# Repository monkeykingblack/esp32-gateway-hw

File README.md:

#ESP32-GATEWAY-HARDWARE

##Features

- ESP32 WIFI, Bluetooth LE, SoC - 240MHz - Module ESP32 Wrover
- Tracking location by GPS-NEO-6M IC
- Send SMS via sim card by 
- Automatic select 3 power sources (DC6-28V, USB and Battery)
- Charger battery lithium 3.7V
- 1 Power LED, 1 Status GPS LED, 1 Status GSM LED

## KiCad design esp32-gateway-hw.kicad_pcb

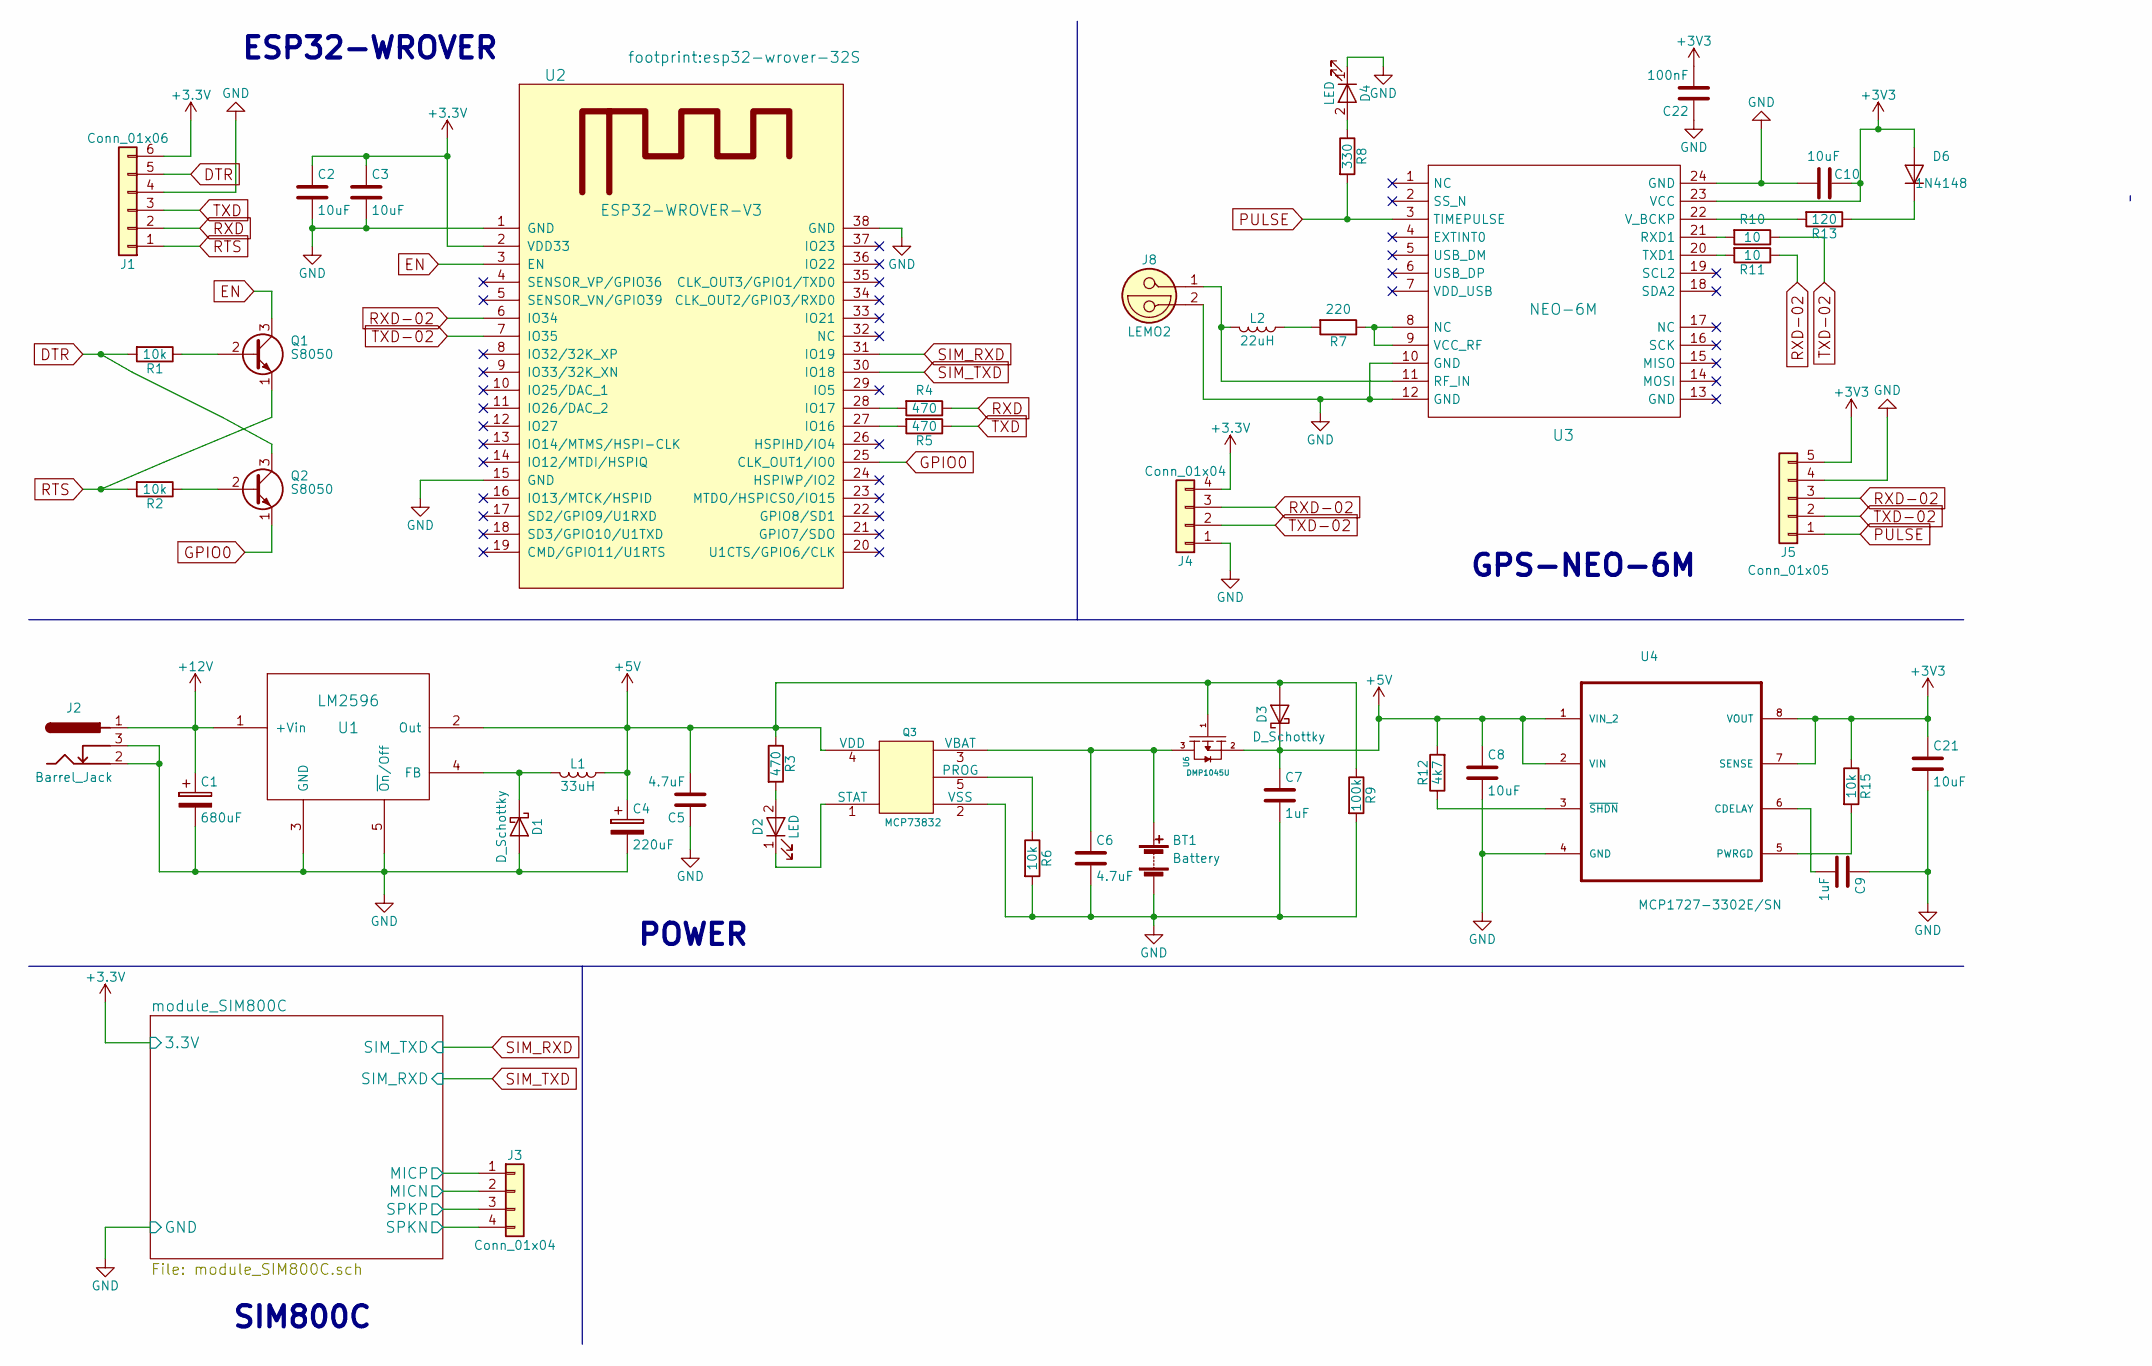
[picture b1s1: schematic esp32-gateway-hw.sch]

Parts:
BT1: Battery; JST_EH_B02B-EH-A_02x2.50mm_Straight
C1: 680uF; CP_Elec_4x5.3
C2, C3, C8, C10, C21: 10uF; C_0603
C4: 220uF; CP_Elec_4x5.3
C5, C6: 4.7uF; C_0603
C7, C9: 1uF; C_0603
C22: 100nF; C_0603
D1, D3: D_Schottky; D_SOD-123
D2, D4: LED; LED_D3.0mm
D6: 1N4148; D_SOD-123
J1: Conn_01x06; Socket_Strip_Straight_1x06_Pitch2.54mm
J2: Barrel_Jack; CUI-PJ-102A_dc-barrel-jack
J3, J4: Conn_01x04; Socket_Strip_Straight_1x04_Pitch2.54mm
J5: Conn_01x05; Socket_Strip_Straight_1x05_Pitch2.54mm
J8: LEMO2; SMA_Straight
L1: 33uH; INDUCTOR_SMD_DIP2
L2: 22uH; INDUCTOR_SMD_DIP2
Q1, Q2: S8050; SOT-23_standar
Q3: MCP73832; SOT-23-5_HandSoldering
R1, R2, R6, R15: 10k; R_0603
R3, R4, R5: 470; R_0603
R7: 220; R_0603
R8: 330; R_0603
R9: 100k; R_0603
R10, R11: 10; R_0603
R12: 4k7; R_0603
R13: 120; R_0603
U1: LM2596; TO-263-5_TabPin3
U2: ESP32-WROVER-V3; esp32-wrover-32S
U3: NEO-6M; GPS24P-SMD-1.1-16X12.2MM
U4: MCP1727-3302E/SN; SOIC-8_3.9x4.9mm_Pitch1.27mm; Digi-Key_Part_Number MCP1727-3302E/SN-ND
U6: DMP1045U; SOT-23

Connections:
+3V3: C2.1, C3.1, C10.1, C21.1, C22.2, D6.2 (A), J1.6, J4.4, J5.5, R15.1, U2.2 (VDD33), U3.23 (VCC), U4.7 (SENSE), U4.8 (VOUT); also elsewhere on the board
+5V: C4.1, C5.2, C7.1, C8.1, D3.1 (K), D3.2 (A), L1.1, Q3.4 (VDD), R3.1, R9.1, R12.2, U1.2 (Out), U4.1 (VIN_2), U4.2 (VIN), U6.1, U6.2
+12V: C1.1, J2.1, U1.1 (+Vin)
/module_SIM800C/MICN: J3.2; also elsewhere on the board
/module_SIM800C/MICP: J3.1; also elsewhere on the board
/module_SIM800C/SPKN: J3.4; also elsewhere on the board
/module_SIM800C/SPKP: J3.3; also elsewhere on the board
DTR: J1.5, Q2.3 (C), R1.2
EN: Q1.3 (C), U2.3 (EN)
GND: BT1.2 (-), C1.2, C2.2, C3.2, C4.2, C5.1, C6.2, C7.2, C8.2, C9.1, C10.2, C21.2, C22.1, D1.2 (A), D4.1 (K), J1.4, J2.2, J2.3, J4.1, J5.4, J8.2, Q3.2 (VSS), R6.2, R9.2, U1.3 (GND), U1.5 (~On~/Off), U2.1 (GND), U2.15 (GND), U2.38 (GND), U3.10 (GND), U3.12 (GND), U3.24 (GND), U4.4 (GND); also elsewhere on the board
GPIO0: Q2.1 (E), U2.25 (CLK_OUT1/IO0)
unnamed: BT1.1 (+), C6.1, Q3.3 (VBAT), U6.3
unnamed: C9.2, U4.6 (CDELAY)
unnamed: D1.1 (K), L1.2, U1.4 (FB)
unnamed: D2.1 (K), Q3.1 (STAT)
unnamed: D2.2 (A), R3.2
unnamed: D4.2 (A), R8.1
unnamed: D6.1 (K), R13.1
unnamed: J8.1, L2.2, U3.11 (RF_IN)
unnamed: L2.1, R7.2
unnamed: Q1.2 (B), R1.1
unnamed: Q2.2 (B), R2.1
unnamed: Q3.5 (PROG), R6.1
unnamed: R4.2, U2.28 (IO17)
unnamed: R5.2, U2.27 (IO16)
unnamed: R7.1, U3.8 (NC), U3.9 (VCC_RF)
unnamed: R10.2, U3.21 (RXD1)
unnamed: R11.2, U3.20 (TXD1)
unnamed: R12.1, U4.3 (~SHDN)
unnamed: R13.2, U3.22 (V_BCKP)
unnamed: R15.2, U4.5 (PWRGD)
PULSE: J5.1, R8.2, U3.3 (TIMEPULSE)
RTS: J1.1, Q1.1 (E), R2.2
RXD: J1.2, R4.1
RXD-02: J4.3, J5.3, R11.1, U2.6 (IO34)
SIM_RXD: U2.31 (IO19); also elsewhere on the board
SIM_TXD: U2.30 (IO18); also elsewhere on the board
TXD: J1.3, R5.1
TXD-02: J4.2, J5.2, R10.1, U2.7 (IO35)

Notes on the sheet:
ESP32-WROVER
GPS-NEO-6M
POWER
SIM800C

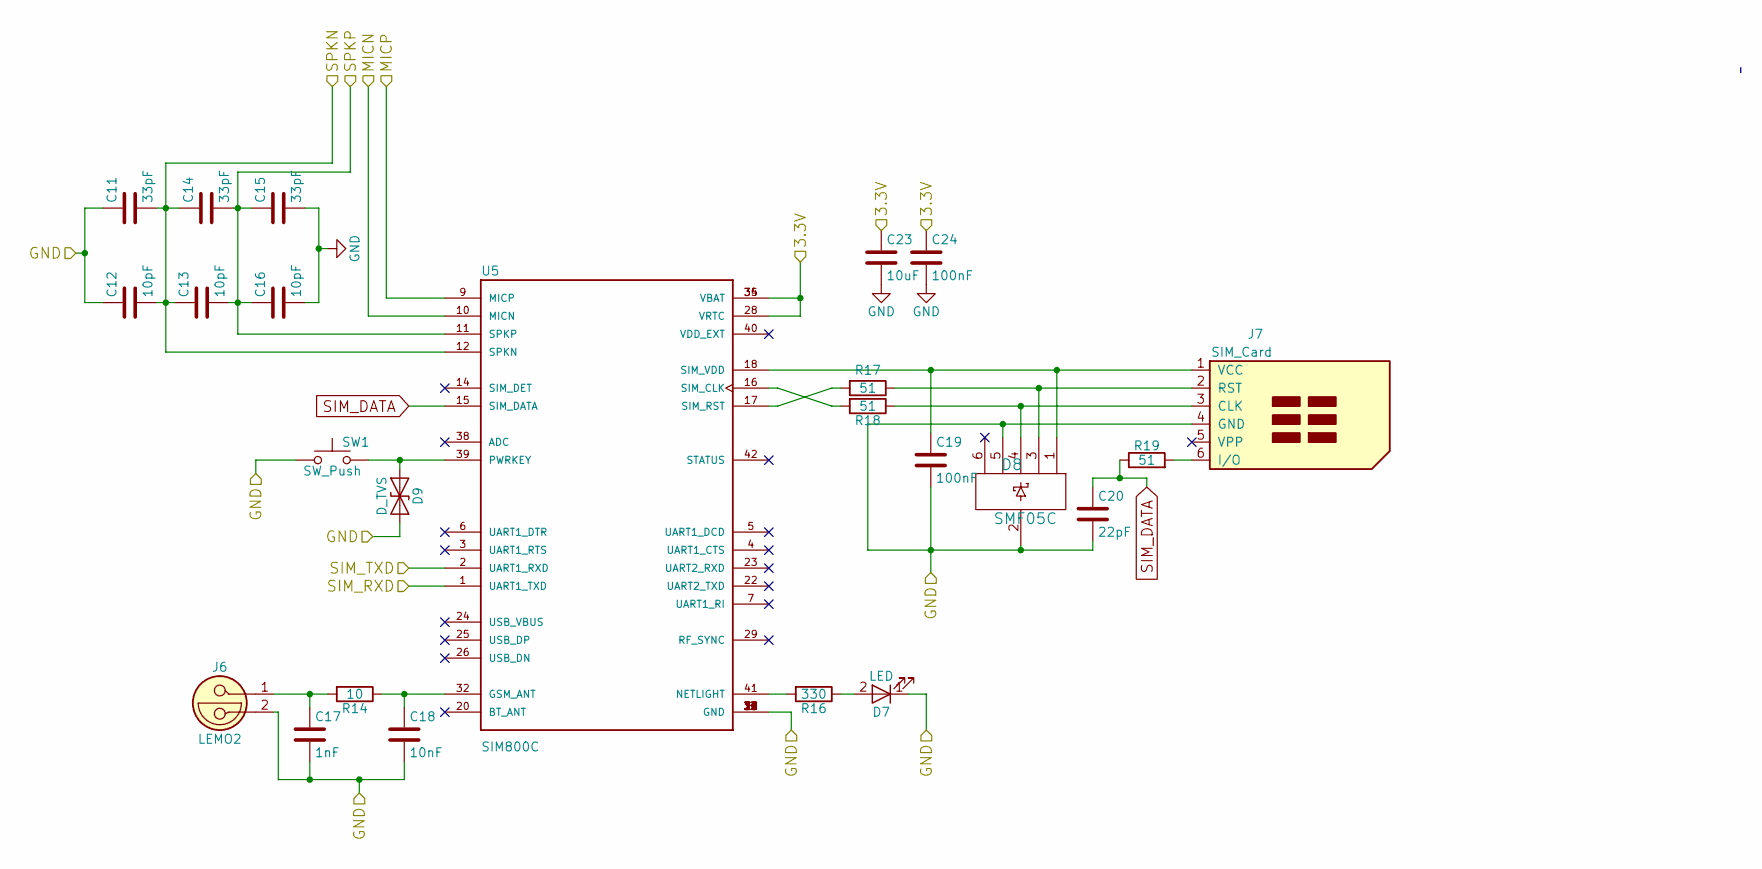
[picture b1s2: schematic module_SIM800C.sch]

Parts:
C11, C14, C15: 33pF; C_0603
C12, C13, C16: 10pF; C_0603
C17: 1nF; C_0603
C18: 10nF; C_0603
C19, C24: 100nF; C_0603
C20: 22pF; C_0603
C23: 10uF; C_0603
D7: LED; LED_D3.0mm
D8: SMF05C; SC70-6L
D9: D_TVS; DO-214AC(SMA)
J6: LEMO2; SMA_Straight
J7: SIM_Card; MOLEX_47553-2001_SIMCARD
R14: 10; R_0603
R16: 330; R_0603
R17, R18, R19: 51; R_0603
SW1: SW_Push; SW_PUSH_6mm_h4.3mm
U5: SIM800C; sim800C

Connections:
+3V3: C23.1, C24.1, U5.28 (VRTC), U5.34 (VBAT), U5.35 (VBAT); also elsewhere on the board
/module_SIM800C/MICN: U5.10 (MICN); also elsewhere on the board
/module_SIM800C/MICP: U5.9 (MICP); also elsewhere on the board
/module_SIM800C/SPKN: C11.2, C12.2, C13.1, C14.1, U5.12 (SPKN); also elsewhere on the board
/module_SIM800C/SPKP: C13.2, C14.2, C15.1, C16.1, U5.11 (SPKP); also elsewhere on the board
GND: C11.1, C12.1, C15.2, C16.2, C17.2, C18.2, C19.2, C20.2, C23.2, C24.2, D7.1 (K), D8.2, D8.5, D9.2 (A2), J6.2, J7.4 (GND), SW1.1, U5.8 (GND), U5.13 (GND), U5.19 (GND), U5.21 (GND), U5.27 (GND), U5.30 (GND), U5.31 (GND), U5.33 (GND), U5.36 (GND), U5.37 (GND); also elsewhere on the board
unnamed: C17.1, J6.1, R14.2
unnamed: C18.1, R14.1, U5.32 (GSM_ANT)
unnamed: C19.1, D8.1, J7.1 (VCC), U5.18 (SIM_VDD)
unnamed: D7.2 (A), R16.1
unnamed: D8.3, J7.2 (RST), R17.1
unnamed: D8.4, J7.3 (CLK), R18.1
unnamed: D9.1 (A1), SW1.2, U5.39 (PWRKEY)
unnamed: J7.6 (I/O), R19.2
unnamed: R16.2, U5.41 (NETLIGHT)
unnamed: R17.2, U5.17 (SIM_RST)
unnamed: R18.2, U5.16 (SIM_CLK)
SIM_DATA: C20.1, R19.1, U5.15 (SIM_DATA)
SIM_RXD: U5.2 (UART1_RXD); also elsewhere on the board
SIM_TXD: U5.1 (UART1_TXD); also elsewhere on the board

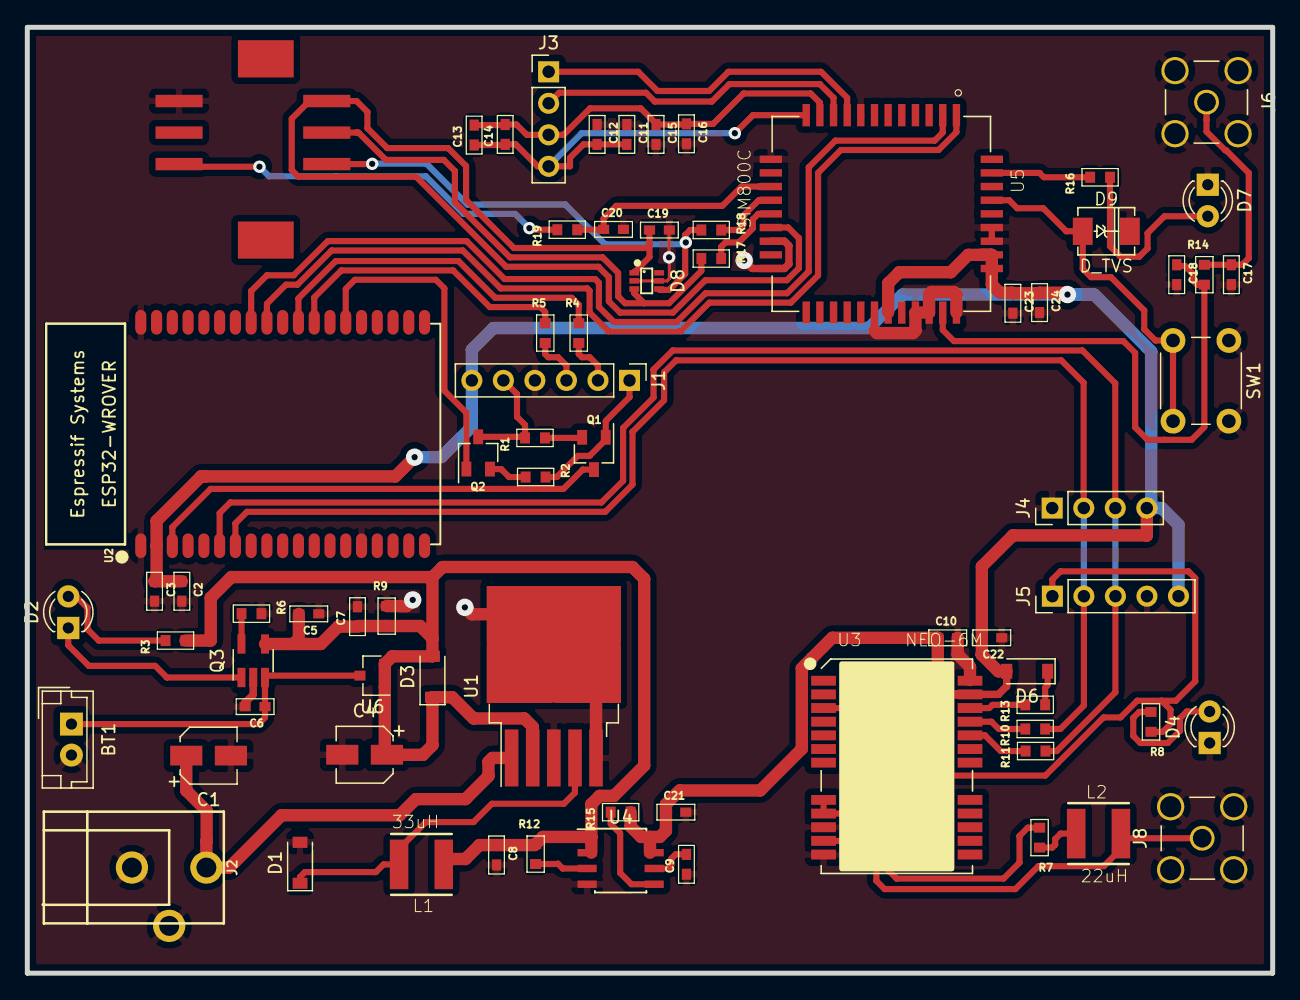
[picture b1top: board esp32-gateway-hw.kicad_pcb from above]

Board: 2 copper layers, 100.3 x 76.2 mm, 72 parts (0 on the bottom side), 51 nets.

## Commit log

2017-10-11 Schematic and footprint all component
2017-10-11 add README
2017-10-11 add gitignore
2017-10-11 fixed untracked files
2017-10-11 fix SIM_Card pin out
2017-10-11 Change C1, C4 to polarized capacitors
2017-10-11 Add button to pin PWRKEY in SIM800C for handle power on SIM800C
2017-10-11 fix UART interface module GPS
2017-10-11 Make PCB
2017-10-17 Change TC1264 to MCP1727
2017-10-17 replace mosfet in Power Module
2017-10-17 add PCB
2017-10-17 add keepout area on anthena of esp32-wrover
2017-10-18 redraw PCB
2017-10-18 add 3D shape
2017-10-18 add RF connector 3D shape
